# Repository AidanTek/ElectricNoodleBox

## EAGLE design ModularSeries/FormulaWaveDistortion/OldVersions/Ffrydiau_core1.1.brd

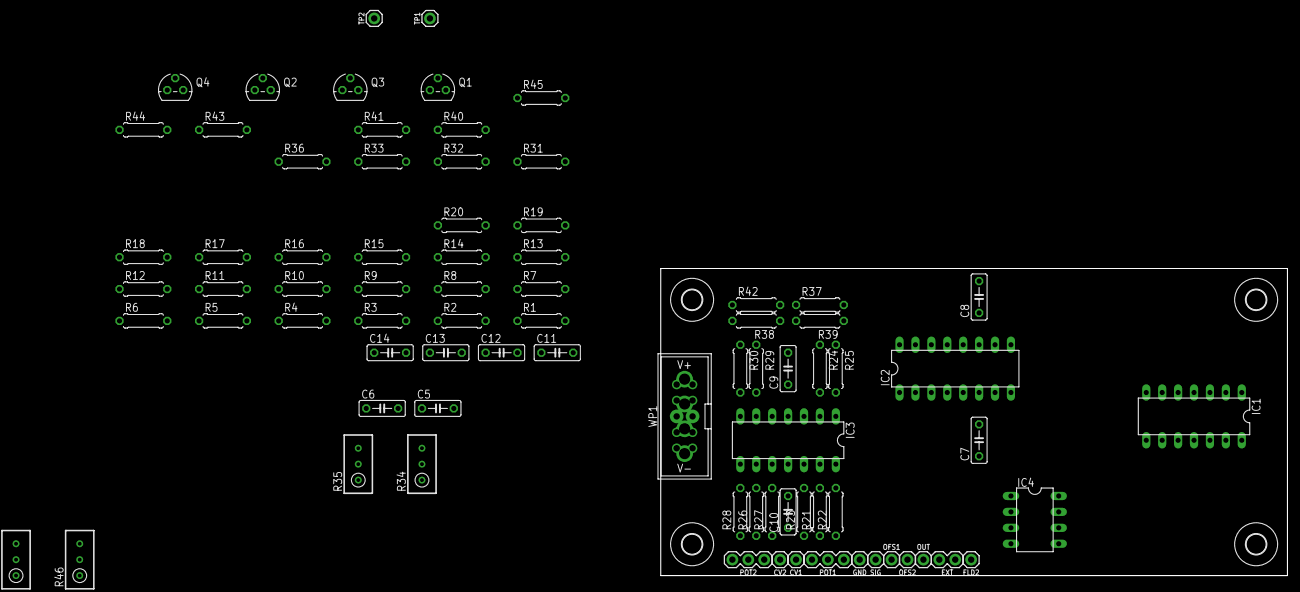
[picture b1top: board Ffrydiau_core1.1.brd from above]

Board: 2 copper layers, 100.0 x 49.0 mm, 83 parts (0 on the bottom side), 48 nets, no tracks yet.

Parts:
C5, C6, C7, C8, C9, C10, C11, C12: 100nF; C050-025X075
C13, C14: 22pF; C050-025X075
CV1, CV2: 1XWIREPAD; 1X01
EXT: 2XWIREPAD; 1X02
FLD2: 1XWIREPAD; 1X01
GND: 1XWIREPAD; 1X01
H1, H2, H3, H4: MOUNT-HOLE3.2; 3,2
IC1, IC3: DIL14
IC2: DIL16
IC4: DIL08
OFS1, OFS2: 1XWIREPAD; 1X01
OUT: 1XWIREPAD; 1X01
POT1, POT2: 3XWIREPAD; 1X03
Q1, Q3: 2N3906; TO92
Q2, Q4: 2N3904; TO92
R1, R12: 30K; 0207/7
R2, R3, R13, R14: 12K; 0207/7
R4, R16: 220K; 0207/7
R5, R6, R7, R15, R41, R44: 10K; 0207/7
R8, R9, R10, R11, R21, R22, R23, R24, R25, R26, R27, R28, R29, R30: 100K; 0207/7
R17, R18: 75K; 0207/7
R19, R20: 22K; 0207/7
R31, R32: 5K7; 0207/7
R33, R36: 15K; 0207/7
R34, R35, R46, R47: 10K; RTRIM3296W
R37, R38, R39, R40, R42, R43: 47K; 0207/7
R45: 100Ω; 0207/7
SIG: 1XWIREPAD; 1X01
TP1, TP2: 1XWIREPAD; 1X01
WP1: COMBO_SUPPLY_HEADER; COMBINED_POWER

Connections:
+12V: C6.1, C8.1, C9.1, C12.1, IC1.4, IC2.11, IC3.4, IC4.8, POT1.3, POT2.3, R2.2, R13.2, R31.1, R32.1, WP1.V+1, WP1.V+2, WP1.V+3
-12V: C5.2, C7.2, C10.2, C11.2, IC1.11, IC2.6, IC3.11, IC4.4, POT1.1, POT2.1, R3.1, R14.1, R37.1, R42.1, WP1.V-1, WP1.V-2, WP1.V-3
AGND: C5.1, C6.2, C7.1, C8.2, C9.2, C10.1, C11.1, C12.2, GND.1, IC1.3, IC1.5, IC1.10, IC1.12, IC3.3, IC3.5, IC3.10, IC3.12, IC4.3, IC4.5, R19.1, R20.1, R34.2, R35.2, R41.2, R44.2, WP1.GND1, WP1.GND2, WP1.GND3, WP1.GND4, WP1.GND5, WP1.GND6, WP1.GND7, WP1.GND8
unnamed: Q1.2, Q2.2, R1.2, R40.1
unnamed: Q1.3, R2.1, R46.3
unnamed: Q2.3, R3.2, R46.1
unnamed: Q1.1, Q2.1, R5.2, R46.2
unnamed: IC1.9, R4.2, R5.1
unnamed: IC1.8, R4.1, R6.2
unnamed: IC1.13, R6.1, R7.2
unnamed: OUT.1, R45.1
unnamed: C13.2, IC4.1, R1.1, R17.2, TP1.1
unnamed: IC1.2, R8.2, R9.1, R10.1, R11.1
unnamed: IC1.1, R8.1, R45.2
unnamed: Q3.2, Q4.2, R12.2, R43.1
unnamed: Q3.3, R13.1, R47.3
unnamed: Q4.3, R14.2, R47.1
unnamed: Q3.1, Q4.1, R15.2, R47.2
unnamed: IC1.6, R15.1, R16.2
unnamed: FLD2.1, IC1.7, R11.2, R16.1
unnamed: C14.1, IC2.12, IC4.6, R18.1, R20.2
unnamed: C13.1, IC2.5, IC4.2, R17.1, R19.2
unnamed: C14.2, IC4.7, R12.1, R18.2, TP2.1
unnamed: IC3.13, R21.2, R22.1, R23.2
unnamed: IC3.14, R22.2, R24.1
unnamed: IC3.2, R24.2, R25.1
unnamed: IC3.1, R25.2, R39.2
unnamed: CV2.1, R27.1
unnamed: IC3.7, R30.2, R38.2
unnamed: POT1.2, R21.1
unnamed: IC3.6, R29.2, R30.1
unnamed: CV1.1, R23.1
unnamed: IC3.8, R28.2, R29.1
unnamed: IC3.9, R26.2, R27.2, R28.1
unnamed: IC2.14, R35.3, R36.2
unnamed: IC2.13, R35.1
unnamed: IC2.15, R31.2
unnamed: IC2.2, R32.2
unnamed: IC2.1, R37.2, R39.1
unnamed: POT2.2, R26.1
unnamed: IC2.3, R33.2, R34.3
unnamed: IC2.4, R34.1
unnamed: IC2.16, R38.1, R42.2
unnamed: OFS1.1, R40.2, R41.1
unnamed: OFS2.1, R43.2, R44.1
unnamed: EXT.2, R36.1
SIGIN: R9.2, R33.1, SIG.1
STAGE1OUT: EXT.1, IC1.14, R7.1, R10.2

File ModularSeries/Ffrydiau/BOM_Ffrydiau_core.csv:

Qty,Value,Package,Parts,Description,RETAILER,CATALOGUE
,,,,,,
16,100K,0207/10,"R4, R8, R9, R10, R11, R16, R21, R22, R23, R24, R25, R26, R27, R28, R29, R30",RESISTOR 1/4W,Farnell,2329853
2,100Ω,0207/10,"R45, R46",RESISTOR 1/4W,Farnell,2329854
7,10K,0207/10,"R5, R6, R7, R12, R15, R41, R44",RESISTOR 1/4W,Farnell,2329855
4,12K,0207/10,"R2, R3, R13, R14",RESISTOR 1/4W,Farnell,2329863
2,15K,0207/10,"R33, R36",RESISTOR 1/4W,Farnell,1563095
2,22K,0207/10,"R19, R20",RESISTOR 1/4W,Farnell,2329901
6,47K,0207/10,"R37, R38, R39, R40, R42, R43",RESISTOR 1/4W,Farnell,2329944
1,4K7,0207/10,R1,RESISTOR 1/4W,Farnell,2329945
2,5K6,0207/10,"R31, R32",RESISTOR 1/4W,Farnell,2329958
2,75K,0207/10,"R17, R18",RESISTOR 1/4W,Farnell,2329972
2,10K,RTRIM3296W,"R34, R35",Trimm resistor 3296W,Farnell,9353186
,,,,,,
2,22pF,C050-025X075,"C13, C14",CAPACITOR Ceramic,Farnell,1457695
8,100nF,C050-025X075,"C5, C6, C7, C8, C9, C10, C11, C12",CAPACITOR Ceramic,Farnell,2797801
3,4.7¬µF,"E2,5-6E","C1, C2, C3","POLARIZED CAPACITOR, Electrolytic 25V+",Farnell,9451234
,,,,,,
2,2N3904,TO92,"Q2, Q4",NPN Transistor TO-92,Farnell,1574370
2,2N3906,TO92,"Q1, Q3",PNP Transistor TO-92,Farnell,1574372
1,LM13700,DIL16,IC2,Dual Transconductance Amplifier with Darlington Buffer,Farnell,3118206
1,TL082,DIL08,IC4,Dual Operational Amplifier,Farnell,1103189
2,TL084,DIL14,"IC1, IC3",Quad Operational Amplifier,Farnell,3005140
,,,,,,
1,Power Header,Power Header,WP1,10 way Shrouded IDC,Farnell,2843527
,,,,,,
9,Jack / Banana Connector,1X01,"CV1, CV2, FLD2, OFS1, OFS2, OUT, SIG, VCA",Banana or Jack patch point (panel part),Farnell,1698951
1,SPDT Mechanical Switch,1X02,EXT,Toggle switch SPDT (panel part),Farnell,9473491
2,B100K Potentiometer,1X03,"POT1, POT2",Taiwan Alpha 16mm (panel part),Rapid,65-0756

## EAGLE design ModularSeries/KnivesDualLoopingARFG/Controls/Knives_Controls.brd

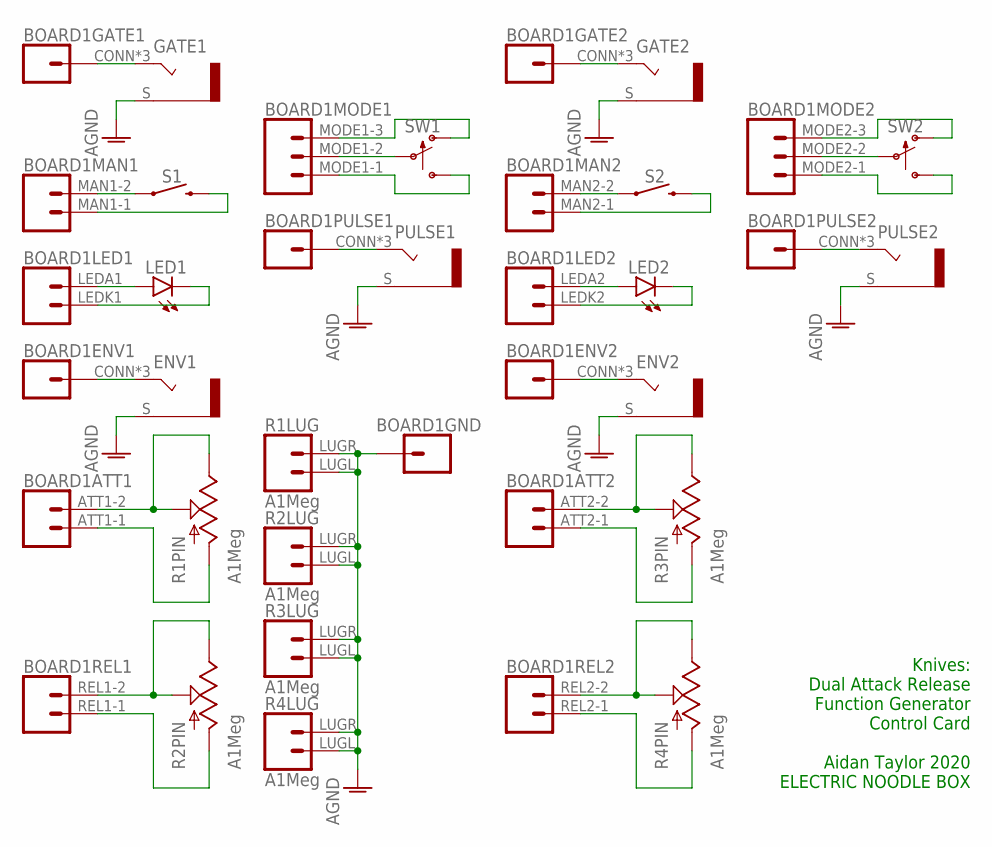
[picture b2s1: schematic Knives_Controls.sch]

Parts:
BOARD1: KNIVES_LINK; KNIVES
ENV1, ENV2: COMBI-JACKCINCHNANA; NEWCOMBOJACK_PANEL
GATE1, GATE2: COMBI-JACKCINCHNANA; NEWCOMBOJACK_PANEL
LED1, LED2: LED3MM
PULSE1, PULSE2: COMBI-JACKCINCHNANA; NEWCOMBOJACK_PANEL
R1, R2, R3, R4: A1Meg; ALPHA_RV09_9MMPOT
S1, S2: MCDTS-2_PUSHBUTTON
SW1, SW2: SPDT_SWITCHDW1; MICRODPDT-DW1

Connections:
AGND: BOARD1.GND (1), ENV1.S, ENV2.S, GATE1.S, GATE2.S, PULSE1.S, PULSE2.S, R1.LUGL (1), R1.LUGR (2), R2.LUGL (1), R2.LUGR (2), R3.LUGL (1), R3.LUGR (2), R4.LUGL (1), R4.LUGR (2)
unnamed: BOARD1.G1 (1), GATE1.CONN (T), GATE1.T1 (T), GATE1.T2 (T)
unnamed: BOARD1.MAN1-2 (2), S1.P$1 (1), S1.P$2 (1)
unnamed: BOARD1.MAN1-1 (1), S1.P$3 (2), S1.P$4 (2)
unnamed: BOARD1.LEDA1 (2), LED1.A
unnamed: BOARD1.LEDK1 (1), LED1.K (C)
unnamed: BOARD1.EOUT1 (1), ENV1.CONN (T), ENV1.T1 (T), ENV1.T2 (T)
unnamed: BOARD1.ATT1-2 (2), R1.C2 (W), R1.C3 (B)
unnamed: BOARD1.ATT1-1 (1), R1.C1 (A)
unnamed: BOARD1.REL1-2 (2), R2.C2 (W), R2.C3 (B)
unnamed: BOARD1.REL1-1 (1), R2.C1 (A)
unnamed: BOARD1.MODE1-1 (1), SW1.C3 (S)
unnamed: BOARD1.MODE1-2 (2), SW1.C2
unnamed: BOARD1.MODE1-3 (3), SW1.C1 (O)
unnamed: BOARD1.P1 (1), PULSE1.CONN (T), PULSE1.T1 (T), PULSE1.T2 (T)
unnamed: BOARD1.G2 (1), GATE2.CONN (T), GATE2.T1 (T), GATE2.T2 (T)
unnamed: BOARD1.MAN2-2 (2), S2.P$1 (1), S2.P$2 (1)
unnamed: BOARD1.MAN2-1 (1), S2.P$3 (2), S2.P$4 (2)
unnamed: BOARD1.LEDA2 (2), LED2.A
unnamed: BOARD1.LEDK2 (1), LED2.K (C)
unnamed: BOARD1.EOUT2 (1), ENV2.CONN (T), ENV2.T1 (T), ENV2.T2 (T)
unnamed: BOARD1.ATT2-2 (2), R3.C2 (W), R3.C3 (B)
unnamed: BOARD1.ATT2-1 (1), R3.C1 (A)
unnamed: BOARD1.REL2-2 (2), R4.C2 (W), R4.C3 (B)
unnamed: BOARD1.REL2-1 (1), R4.C1 (A)
unnamed: BOARD1.MODE2-1 (1), SW2.C3 (S)
unnamed: BOARD1.MODE2-2 (2), SW2.C2
unnamed: BOARD1.MODE2-3 (3), SW2.C1 (O)
unnamed: BOARD1.P2 (1), PULSE2.CONN (T), PULSE2.T1 (T), PULSE2.T2 (T)

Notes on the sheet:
Knives: Dual Attack Release Function Generator Control Card Aidan Taylor 2020 ELECTRIC NOODLE BOX

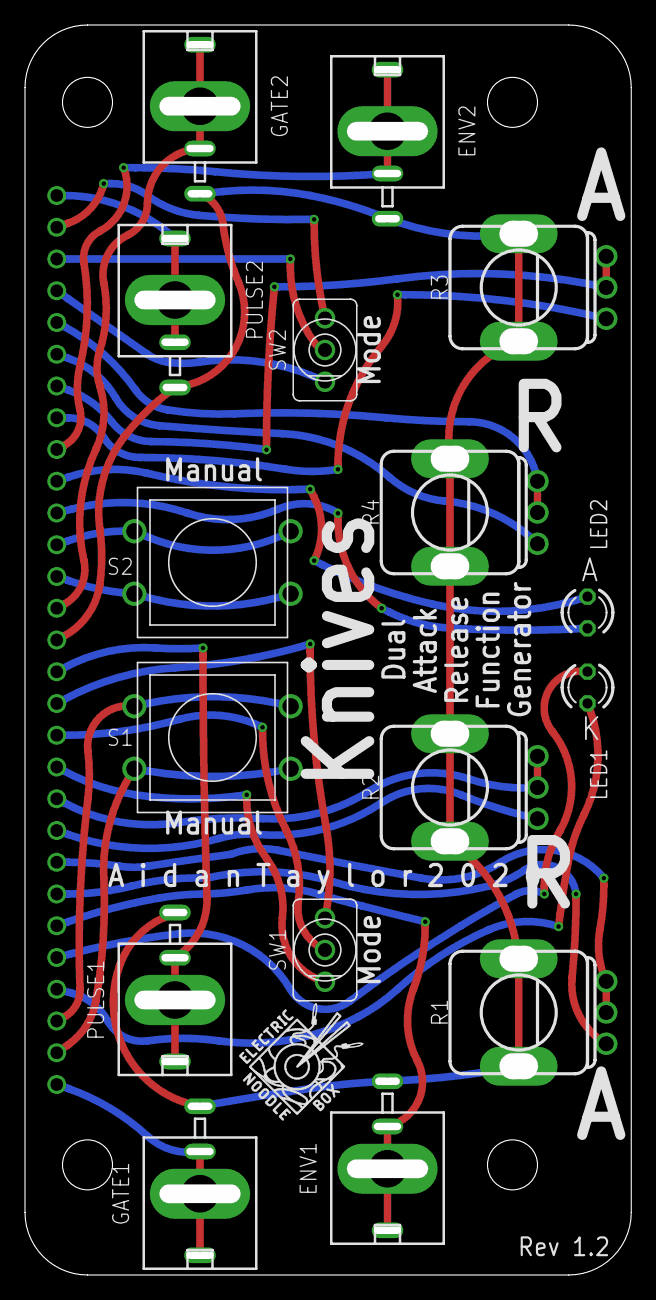
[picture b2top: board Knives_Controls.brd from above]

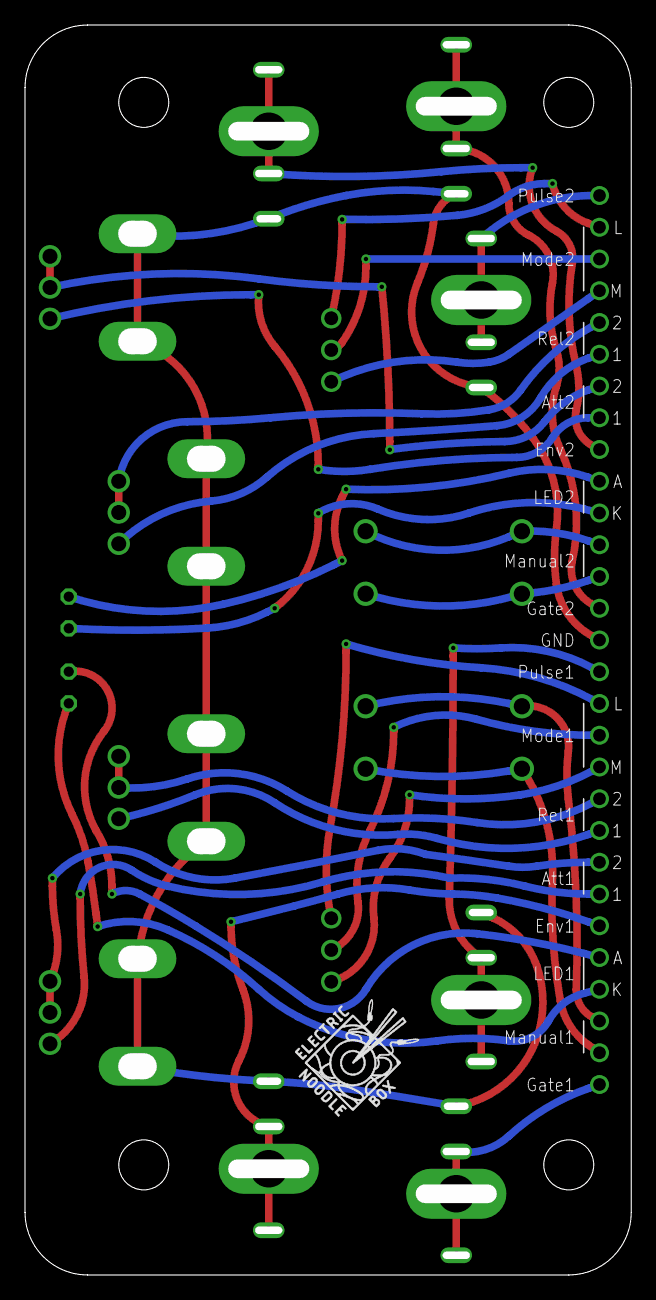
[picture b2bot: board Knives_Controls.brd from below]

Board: 2 copper layers, 48.5 x 100.0 mm, 19 parts (2 on the bottom side), 29 nets.

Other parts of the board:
U$1, U$2: LOGO10X10

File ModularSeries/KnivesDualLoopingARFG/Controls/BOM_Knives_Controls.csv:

Qty,Value,Package,Parts,Description,Retailer,Catalogue
2,,LED3MM,"LED1, LED2",LED 3mm Red,Farnell,1581121
4,A1Meg,ALPHA_RV09_9MMPOT,"R1, R2, R3, R4",Taiwan Alpha 9mm Potentiometer,Thonk,D-shaft A1M
2,BANANA_PANEL,BANANA_PANEL,"ENV1, ENV2",Cinch Green Banana Socket,Mouser,530-1080904-1
2,BANANA_PANEL,BANANA_PANEL,"PULSE1, PULSE2",Cinch White Banana Socket,Mouser,530-108-0901-1
2,BANANA_PANEL,BANANA_PANEL,"GATE1, GATE2",Cinch Violet Banana Socket,Mouser,530-108-0912-1
2,MCDTS-2_PUSHBUTTON,MCDTS-2_PUSHBUTTON,"S1, S2",MCDTS-2 Series Momentary Switch,Farnell,2543105
2,SPDT_SWITCHDW1,MICRODPDT-DW1,"SW1, SW2",SPDT Dailywell Toggle Switch,Thonk,DW1
2,MCDTS-2 Cap,MCDTS-2 Cap,"S1, S2",MCDTS-2 Series Cap KTSC-22R Red,Farnell,9561536
4,Small Knob,Small Knob,"R1, R2, R3, R4",SIFAM/SELCO Small Grey,Thonk,Small Grey
4,Small Green Cap,Small Green Cap,"R1, R2, R3, R4",SIFAM/SELCO Cap Green Small,Thonk,Small Green
4,Male Header,Male Header,,8way 1row 2.54mm Header Male,Farnell,2856626
4,Female Header,Female Header,,8way 1row 2.54mm Header Female,Farnell,1668208
4,M3 Standoff,M3 Standoff,,8mm Standoff Nylon,Farnell,1466945
4,M3 Screw,M3 Screw,,Stainless Steel M3,Farnell,1420032

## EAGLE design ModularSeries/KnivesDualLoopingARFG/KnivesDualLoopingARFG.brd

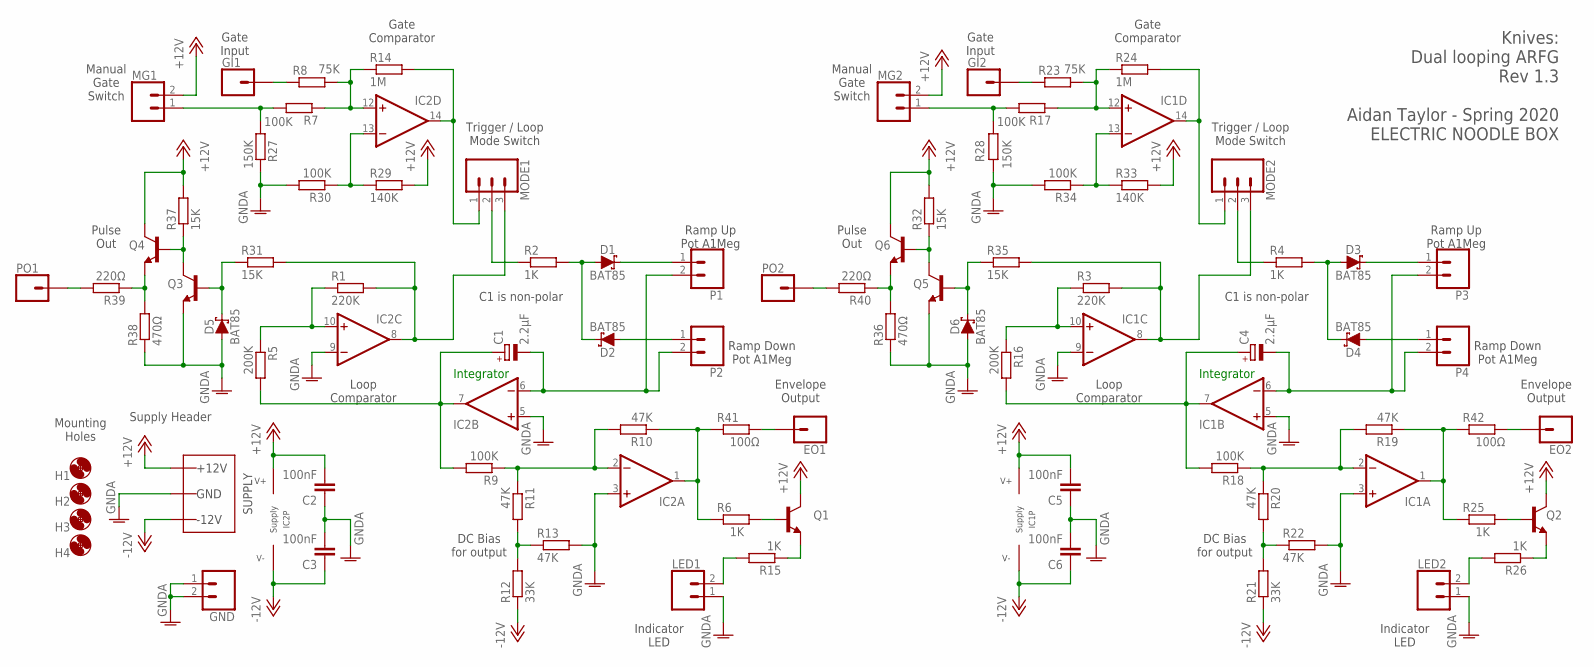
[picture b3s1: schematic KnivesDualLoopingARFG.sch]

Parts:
C1, C4: 2.2µF; E2-5
C2, C3, C5, C6: 100nF; C050-025X075
D1, D2, D3, D4, D5, D6: BAT85; DO35-7
EO1, EO2: 1XWIREPAD; 1X01
GI1, GI2: 1XWIREPAD; 1X01
GND: 2XWIREPAD; 1X02
H1, H2, H3, H4: MOUNT-HOLE3.2; 3,2
IC1, IC2: TL0X4DIL; DIL14
LED1, LED2: 2XWIREPAD; 1X02
MG1, MG2: 2XWIREPAD; 1X02
MODE1, MODE2: 3XWIREPAD; 1X03
P1, P2, P3, P4: 2XWIREPAD; 1X02
PO1, PO2: 1XWIREPAD; 1X01
Q1, Q2, Q3, Q4, Q5, Q6: 2N3904; TO92
R1, R3: 220K; 0207/10
R2, R4, R6, R15, R25, R26: 1K; 0207/10
R5, R16: 200K; 0207/10
R7, R9, R17, R18, R30, R34: 100K; 0207/10
R8, R23: 75K; 0207/10
R10, R11, R13, R19, R20, R22: 47K; 0207/10
R12, R21: 33K; 0207/10
R14, R24: 1M; 0207/10
R27, R28: 150K; 0207/10
R29, R33: 140K; 0207/10
R31, R32, R35, R37: 15K; 0207/10
R36, R38: 470Ω; 0207/10
R39, R40: 220Ω; 0207/10
R41, R42: 100Ω; 0207/10
WP1: COMBO_SUPPLY_HEADER; COMBINED_POWER

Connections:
+12V: C2.2, C5.2, IC1.4 (V+), IC2.4 (V+), MG1.2, MG2.2, Q1.1 (C), Q2.1 (C), Q4.1 (C), Q6.1 (C), R29.2, R32.2, R33.2, R37.2, WP1.V+1 (V++), WP1.V+2 (V++), WP1.V+3 (V++)
-12V: C3.1, C6.1, IC1.11 (V-), IC2.11 (V-), R12.1, R21.1, WP1.V-1 (V--), WP1.V-2 (V--), WP1.V-3 (V--)
ENV1_TRIG: GI1.1, R8.1
ENV1_TRIG1: GI2.1, R23.1
ENVELOPE_OUTPUT: IC2.1 (OUT), R6.1, R10.1, R41.1
ENVELOPE_OUTPUT1: IC1.1 (OUT), R19.1, R25.1, R42.1
GNDA: C2.1, C3.2, C5.1, C6.2, D5.A, D6.A, GND.1, GND.2, IC1.3 (+IN), IC1.5 (+IN), IC1.9 (-IN), IC2.3 (+IN), IC2.5 (+IN), IC2.9 (-IN), LED1.1, LED2.1, Q3.3 (E), Q5.3 (E), R13.2, R22.2, R27.2, R28.2, R30.2, R34.2, R36.1, R38.1, WP1.GND1 (AGND), WP1.GND2 (AGND), WP1.GND3 (AGND), WP1.GND4 (AGND), WP1.GND5 (AGND), WP1.GND6 (AGND), WP1.GND7 (AGND), WP1.GND8 (AGND)
unnamed: Q5.1 (C), Q6.2 (B), R32.1
unnamed: D1.A, D2.C, R2.2
unnamed: D1.C, P1.1
unnamed: D2.A, P2.1
unnamed: C1.-, IC2.6 (-IN), P1.2, P2.2
unnamed: Q1.2 (B), R6.2
unnamed: C1.+, IC2.7 (OUT), R5.2, R9.2
unnamed: IC2.10 (+IN), R1.1, R5.1
unnamed: IC2.2 (-IN), R9.1, R10.2, R11.1
unnamed: Q1.3 (E), R15.1
unnamed: R11.2, R12.2, R13.1
unnamed: MG1.1, R7.2, R27.1
unnamed: IC2.12 (+IN), R7.1, R8.2, R14.1
unnamed: MODE1.2, R2.1
unnamed: IC2.14 (OUT), MODE1.1, R14.2
unnamed: LED1.2, R15.2
unnamed: IC1.8 (OUT), MODE2.3, R3.2, R35.2
unnamed: D3.A, D4.C, R4.2
unnamed: D4.A, P4.1
unnamed: C4.-, IC1.6 (-IN), P3.2, P4.2
unnamed: C4.+, IC1.7 (OUT), R16.2, R18.2
unnamed: IC1.10 (+IN), R3.1, R16.1
unnamed: IC1.2 (-IN), R18.1, R19.2, R20.1
unnamed: R20.2, R21.2, R22.1
unnamed: MG2.1, R17.2, R28.1
unnamed: IC1.12 (+IN), R17.1, R23.2, R24.1
unnamed: IC1.14 (OUT), MODE2.1, R24.2
unnamed: MODE2.2, R4.1
unnamed: Q2.2 (B), R25.2
unnamed: Q2.3 (E), R26.1
unnamed: LED2.2, R26.2
unnamed: D3.C, P3.1
unnamed: IC2.13 (-IN), R29.1, R30.1
unnamed: D5.C, Q3.2 (B), R31.1
unnamed: IC1.13 (-IN), R33.1, R34.1
unnamed: D6.C, Q5.2 (B), R35.1
unnamed: Q3.1 (C), Q4.2 (B), R37.1
unnamed: Q4.3 (E), R38.2, R39.1
unnamed: IC2.8 (OUT), MODE1.3, R1.2, R31.2
unnamed: Q6.3 (E), R36.2, R40.1
unnamed: PO1.1, R39.2
unnamed: PO2.1, R40.2
unnamed: EO1.1, R41.2
unnamed: EO2.1, R42.2

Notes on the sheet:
DC Bias for output
Integrator
Gate Comparator
Loop Comparator
Trigger / Loop Mode Switch
C1 is non-polar
Ramp Up Pot A1Meg
Ramp Down Pot A1Meg
Indicator LED
Manual Gate Switch
Gate Input
Envelope Output
Knives: Dual looping ARFG Rev 1.3 Aidan Taylor - Spring 2020 ELECTRIC NOODLE BOX
Supply Header
Mounting Holes
Pulse Out

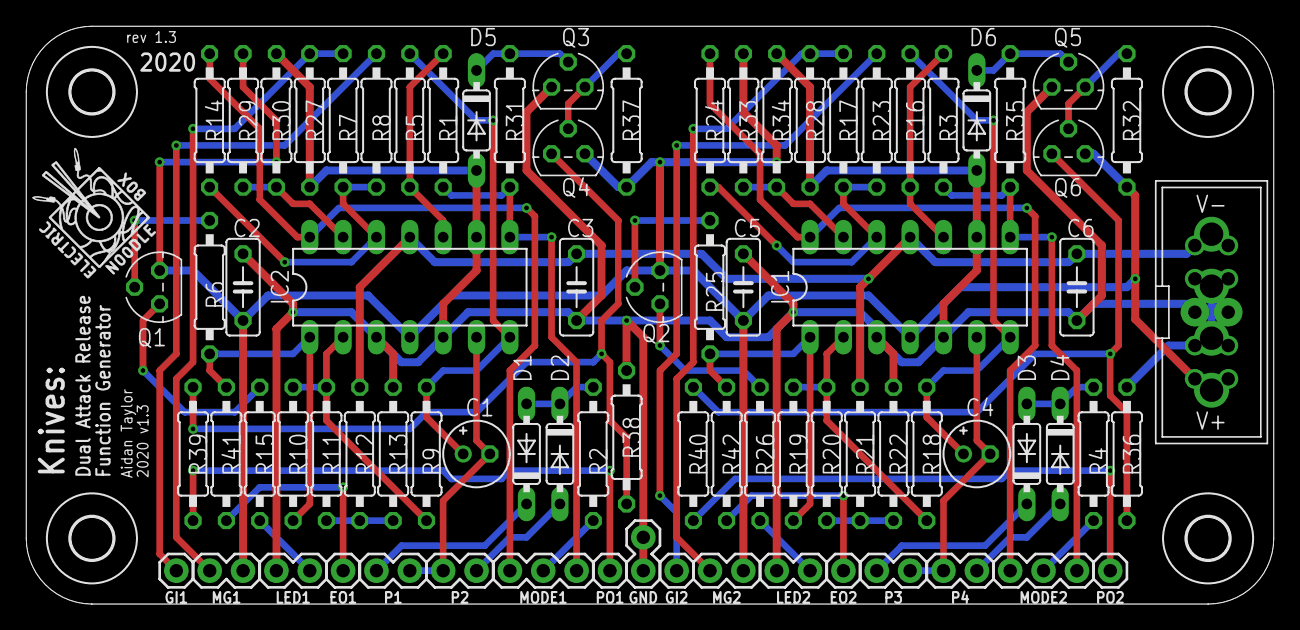
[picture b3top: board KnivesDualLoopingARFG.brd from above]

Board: 2 copper layers, 95.0 x 44.0 mm, 86 parts (1 on the bottom side), 51 nets.

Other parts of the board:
U$1, U$2: LOGO10X10

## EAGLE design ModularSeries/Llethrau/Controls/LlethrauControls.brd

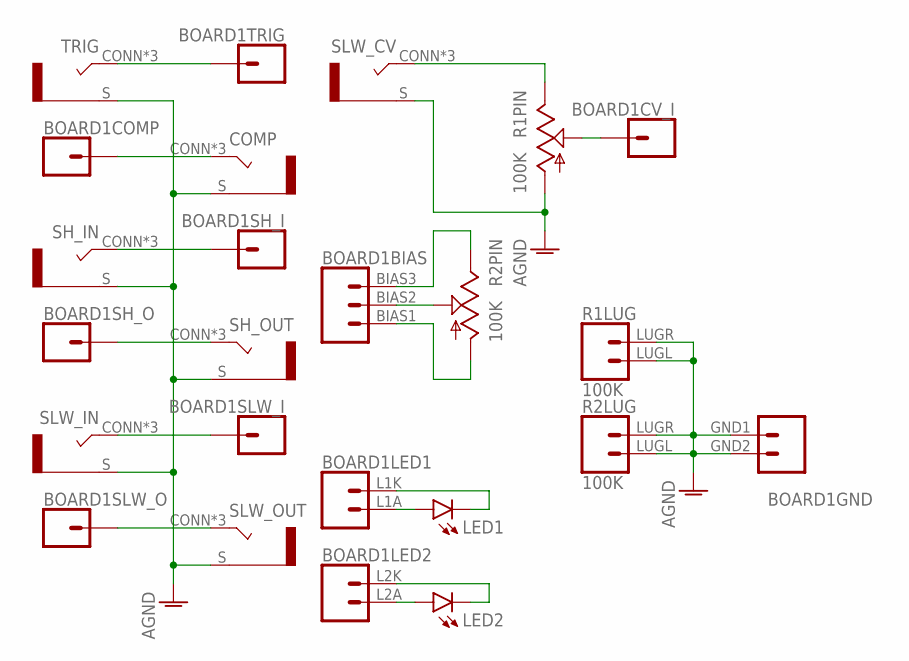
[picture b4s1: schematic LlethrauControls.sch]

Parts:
BOARD1: LLETHRAU_LINK; LLETHRAU
COMP: COMBI-JACKCINCHNANA; NEWCOMBOJACK_PANEL
LED1, LED2: LED5MM
R1, R2: 100K; ALPHA_RV09_9MMPOT
SH_IN: COMBI-JACKCINCHNANA; NEWCOMBOJACK_PANEL
SH_OUT: COMBI-JACKCINCHNANA; NEWCOMBOJACK_PANEL
SLW_CV: COMBI-JACKCINCHNANA; NEWCOMBOJACK_PANEL
SLW_IN: COMBI-JACKCINCHNANA; NEWCOMBOJACK_PANEL
SLW_OUT: COMBI-JACKCINCHNANA; NEWCOMBOJACK_PANEL
TRIG: COMBI-JACKCINCHNANA; NEWCOMBOJACK_PANEL

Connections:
AGND: BOARD1.GND1 (1), BOARD1.GND2 (2), COMP.S, R1.C1 (A), R1.LUGL (1), R1.LUGR (2), R2.LUGL (1), R2.LUGR (2), SH_IN.S, SH_OUT.S, SLW_CV.S, SLW_IN.S, SLW_OUT.S, TRIG.S
unnamed: BOARD1.TRIG (1), TRIG.CONN (T), TRIG.T1 (T), TRIG.T2 (T)
unnamed: BOARD1.COMP (1), COMP.CONN (T), COMP.T1 (T), COMP.T2 (T)
unnamed: BOARD1.SH_I (1), SH_IN.CONN (T), SH_IN.T1 (T), SH_IN.T2 (T)
unnamed: BOARD1.SH_O (1), SH_OUT.CONN (T), SH_OUT.T1 (T), SH_OUT.T2 (T)
unnamed: BOARD1.SLW_I (1), SLW_IN.CONN (T), SLW_IN.T1 (T), SLW_IN.T2 (T)
unnamed: BOARD1.SLW_O (1), SLW_OUT.CONN (T), SLW_OUT.T1 (T), SLW_OUT.T2 (T)
unnamed: BOARD1.BIAS1 (1), R2.C1 (A)
unnamed: BOARD1.BIAS2 (2), R2.C2 (W)
unnamed: BOARD1.BIAS3 (3), R2.C3 (B)
unnamed: BOARD1.L2A (1), LED2.A
unnamed: R1.C3 (B), SLW_CV.CONN (T), SLW_CV.T1 (T), SLW_CV.T2 (T)
unnamed: BOARD1.CV_I (1), R1.C2 (W)
unnamed: BOARD1.L2K (2), LED2.K (C)
unnamed: BOARD1.L1A (1), LED1.A
unnamed: BOARD1.L1K (2), LED1.K (C)

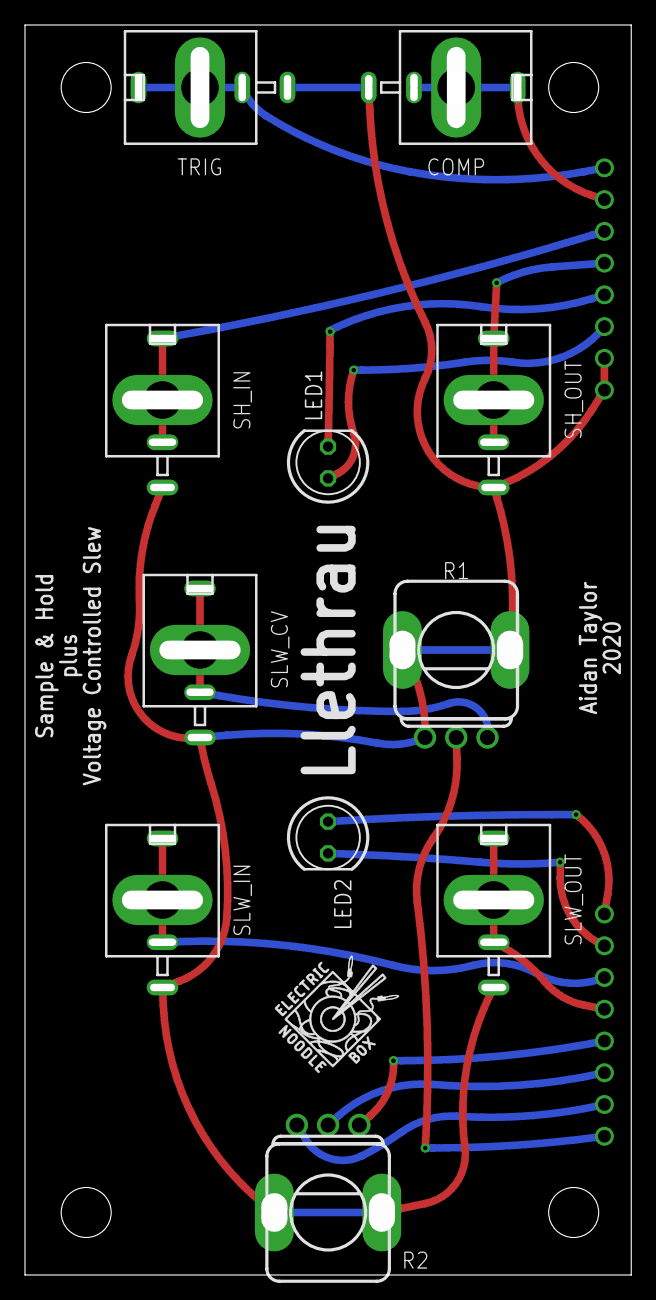
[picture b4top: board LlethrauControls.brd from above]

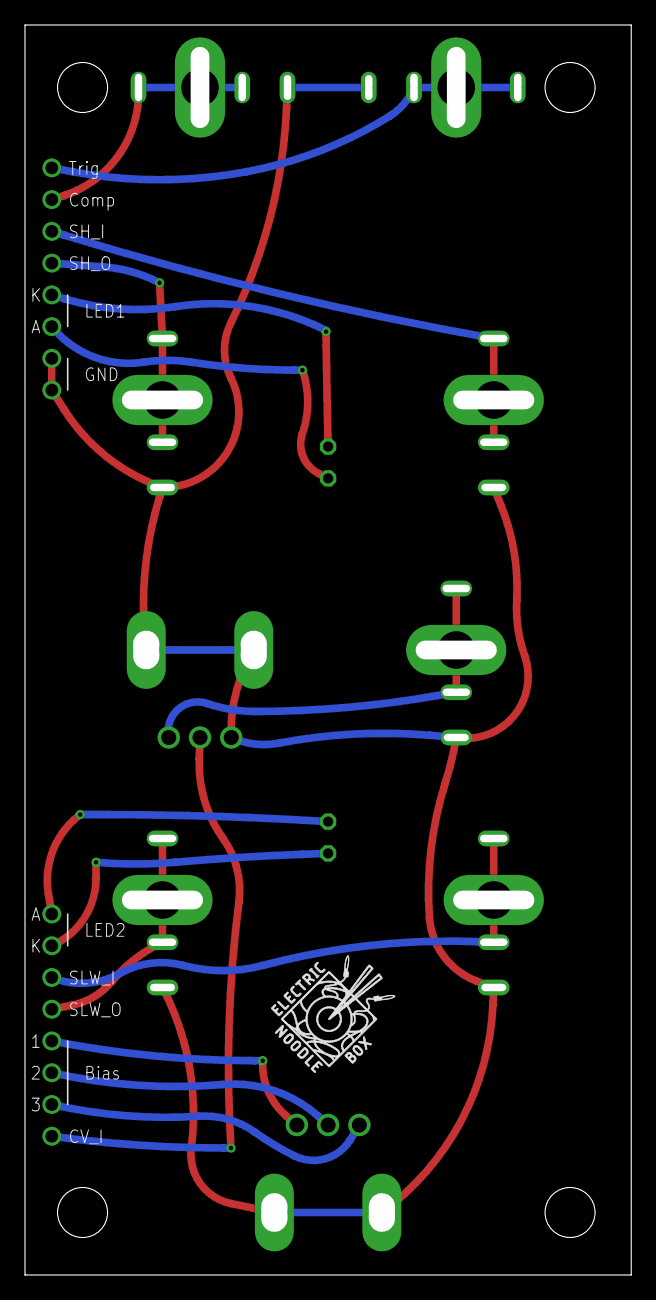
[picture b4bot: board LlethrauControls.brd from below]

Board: 2 copper layers, 48.5 x 100.0 mm, 14 parts (2 on the bottom side), 16 nets.

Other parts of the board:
U$1, U$2: LOGO10X10

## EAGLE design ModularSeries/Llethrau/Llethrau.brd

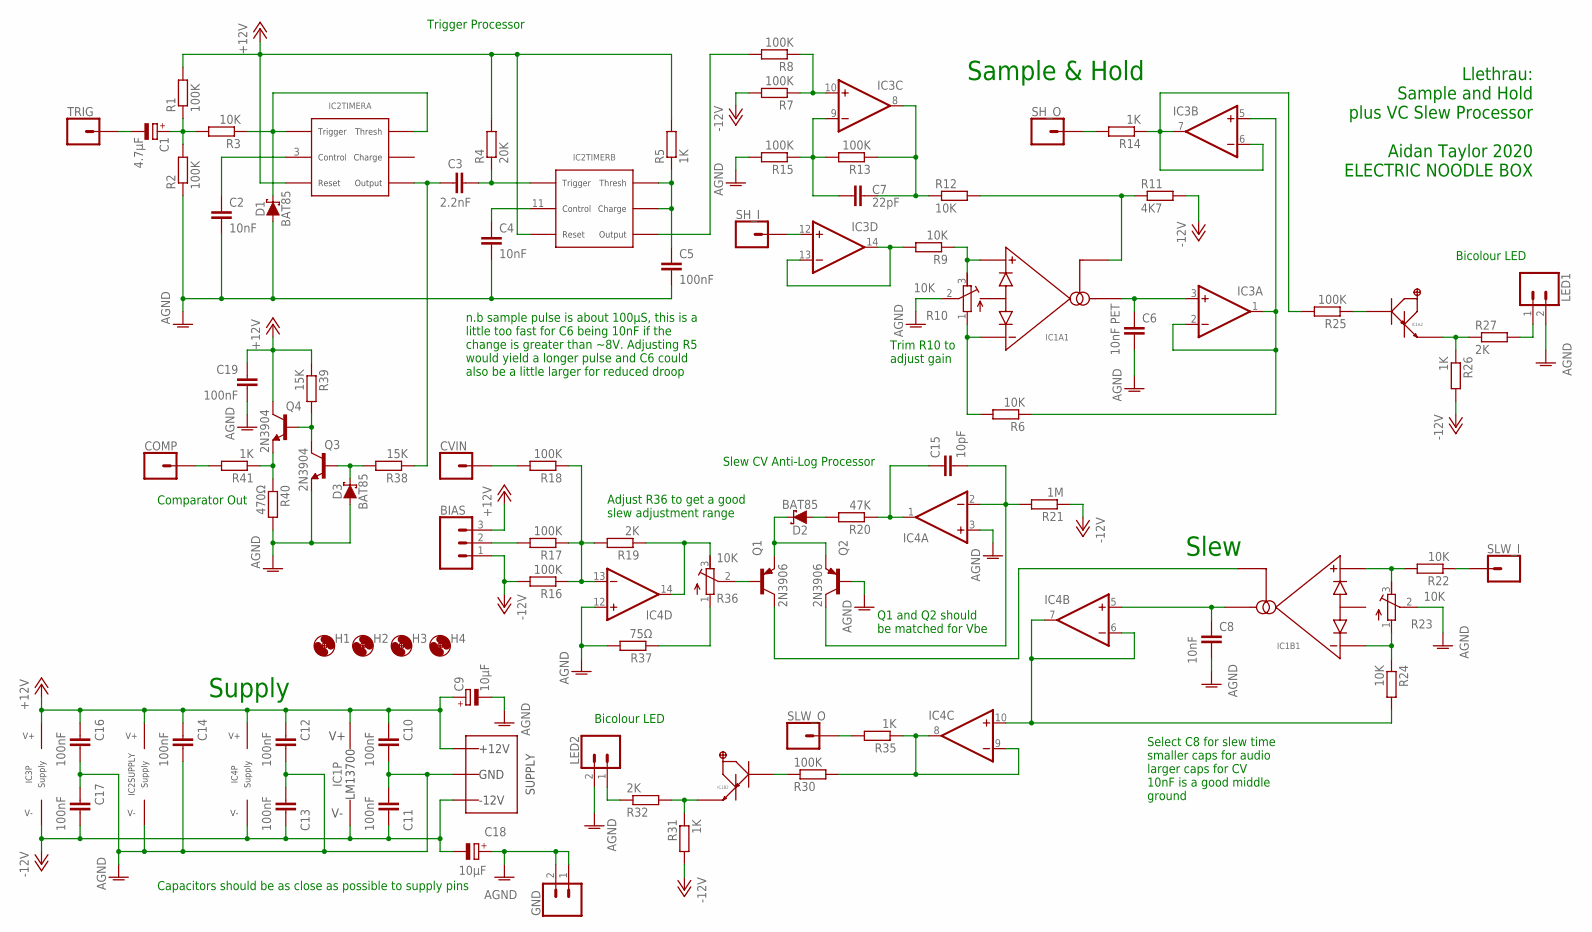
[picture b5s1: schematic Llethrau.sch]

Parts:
BIAS: 3XWIREPAD; 1X03
C1: 4.7µF; E2,5-5
C2, C4, C8: 10nF; C050-025X075
C3: 2.2nF; C050-025X075
C5, C10, C11, C12, C13, C14, C16, C17, C19: 100nF; C050-025X075
C6: 10nF PET; C050-025X075
C7: 22pF; C050-025X075
C9, C18: 10µF; E2,5-5
C15: 10pF; C050-025X075
COMP: 1XWIREPAD; 1X01
CVIN: 1XWIREPAD; 1X01
D1, D2, D3: BAT85; DO35-7
GND: 2XWIREPAD; 1X02
H1, H2, H3, H4: MOUNT-HOLE3.2; 3,2
IC1: LM13700DIL; DIL16
IC2: 556_DUALTIMERDIL14; DIL14
IC3, IC4: TL0X4DIL; DIL14
LED1, LED2: 2XWIREPAD; 1X02
Q1, Q2: 2N3906; TO92
Q3, Q4: 2N3904; TO92
R1, R2, R7, R8, R13, R15, R16, R17, R18, R25, R30: 100K; 0207/7
R3, R6, R9, R12, R22, R24: 10K; 0207/7
R4: 20K; 0207/7
R5, R14, R26, R31, R35, R41: 1K; 0207/7
R10, R23, R36: 10K; RTRIM3296W
R11: 4K7; 0207/7
R19, R27, R32: 2K; 0207/7
R20: 47K; 0207/7
R21: 1M; 0207/7
R37: 75Ω; 0207/7
R38, R39: 15K; 0207/7
R40: 470Ω; 0207/7
SH_I: 1XWIREPAD; 1X01
SH_O: 1XWIREPAD; 1X01
SLW_I: 1XWIREPAD; 1X01
SLW_O: 1XWIREPAD; 1X01
TRIG: 1XWIREPAD; 1X01
WP1: COMBO_SUPPLY_HEADER; COMBINED_POWER

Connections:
+12V: BIAS.3, C9.+, C10.1, C12.1, C14.1, C16.1, C19.1, IC1.11 (V+), IC2.4 (RESET), IC2.10 (RESET), IC2.14 (V+), IC3.4 (V+), IC4.4 (V+), Q4.1 (C), R1.2, R4.2, R5.2, R39.1, WP1.V+1 (V++), WP1.V+2 (V++), WP1.V+3 (V++)
-12V: BIAS.1, C11.2, C13.2, C17.2, C18.-, IC1.6 (V-), IC3.11 (V-), IC4.11 (V-), R7.2, R11.2, R16.2, R21.1, R26.2, R31.2, WP1.V-1 (V--), WP1.V-2 (V--), WP1.V-3 (V--)
AGND: C2.2, C4.2, C5.2, C6.2, C8.2, C9.-, C10.2, C11.1, C12.2, C13.1, C14.2, C16.2, C17.1, C18.+, C19.2, D1.A, D3.A, GND.1, GND.2, IC2.7 (V-), IC4.3 (+IN), IC4.12 (+IN), LED1.2, LED2.2, Q2.2 (B), Q3.3 (E), R2.1, R10.2 (S), R15.2, R23.2 (S), R37.2, R40.2, WP1.GND1 (AGND), WP1.GND2 (AGND), WP1.GND3 (AGND), WP1.GND4 (AGND), WP1.GND5 (AGND), WP1.GND6 (AGND), WP1.GND7 (AGND), WP1.GND8 (AGND)
unnamed: D1.C, IC2.2 (THRESHOLD), IC2.6 (TRIGGER), R3.1
unnamed: C1.+, R1.1, R2.2, R3.2
unnamed: LED1.1, R27.2
unnamed: C3.1, IC2.5 (OUTPUT), R38.1
unnamed: C5.1, IC2.12 (THRESHOLD), IC2.13 (DISCHARGE), R5.1
unnamed: C2.1, IC2.3 (CONT)
unnamed: C3.2, IC2.8 (TRIGGER), R4.1
unnamed: C4.1, IC2.11 (CONT)
unnamed: IC2.9 (OUTPUT), R8.2
unnamed: IC3.10 (+IN), R7.1, R8.1
unnamed: C7.2, IC3.8 (OUT), R12.1, R13.1
unnamed: C6.1, IC1.5 (AMPOUT), IC3.3 (+IN)
unnamed: IC3.1 (OUT), IC3.2 (-IN), IC3.5 (+IN), R6.1
unnamed: IC1.1 (AMPBIAS), R11.1, R12.2
unnamed: IC1.4 (AMP-), R6.2, R10.1 (A)
unnamed: IC1.3 (AMP+), R9.1, R10.3 (E)
unnamed: IC3.13 (-IN), IC3.14 (OUT), R9.2
unnamed: C1.-, TRIG.1
unnamed: IC3.12 (+IN), SH_I.1
unnamed: IC3.6 (-IN), IC3.7 (OUT), R14.1, R25.2
unnamed: R14.2, SH_O.1
unnamed: D2.C, Q1.3 (E), Q2.3 (E)
unnamed: C7.1, IC3.9 (-IN), R13.2, R15.1
unnamed: IC4.13 (-IN), R16.1, R17.1, R18.1, R19.2
unnamed: IC4.14 (OUT), R19.1, R36.3 (E)
unnamed: D2.A, R20.2
unnamed: IC4.6 (-IN), IC4.7 (OUT), IC4.10 (+IN), R24.2
unnamed: BIAS.2, R17.2
unnamed: CVIN.1, R18.2
unnamed: IC1.14 (AMP+), R22.2, R23.3 (E)
unnamed: R36.1 (A), R37.1
unnamed: Q1.2 (B), R36.2 (S)
unnamed: IC1.13 (AMP-), R23.1 (A), R24.1
unnamed: COMP.1, R41.2
unnamed: D3.C, Q3.2 (B), R38.2
unnamed: C8.1, IC1.12 (AMPOUT), IC4.5 (+IN)
unnamed: IC1.16 (AMPBIAS), Q1.1 (C)
unnamed: IC4.8 (OUT), IC4.9 (-IN), R30.2, R35.1
unnamed: IC1.7 (BUFF_IN), R25.1
unnamed: IC1.8 (BUFF_OUT), R26.1, R27.1
unnamed: LED2.1, R32.1
unnamed: IC1.10 (BUFF_IN), R30.1
unnamed: IC1.9 (BUFF_OUT), R31.1, R32.2
unnamed: R35.2, SLW_O.1
unnamed: C15.1, IC4.1 (OUT), R20.1
unnamed: C15.2, IC4.2 (-IN), Q2.1 (C), R21.2
unnamed: R22.1, SLW_I.1
unnamed: Q3.1 (C), Q4.2 (B), R39.2
unnamed: Q4.3 (E), R40.1, R41.1

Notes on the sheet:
Trim R10 to adjust gain
n.b sample pulse is about 100µS, this is a little too fast for C6 being 10nF if the change is greater than ~8V. Adjusting R5 would yield a longer pulse and C6 could also be a little larger for reduced droop
Select C8 for slew time smaller caps for audio larger caps for CV 10nF is a good middle ground
Sample & Hold
Slew
Supply
Capacitors should be as close as possible to supply pins
Bicolour LED
Llethrau: Sample and Hold plus VC Slew Processor Aidan Taylor 2020 ELECTRIC NOODLE BOX
Trigger Processor
Slew CV Anti-Log Processor
Adjust R36 to get a good slew adjustment range
Comparator Out
Q1 and Q2 should be matched for Vbe

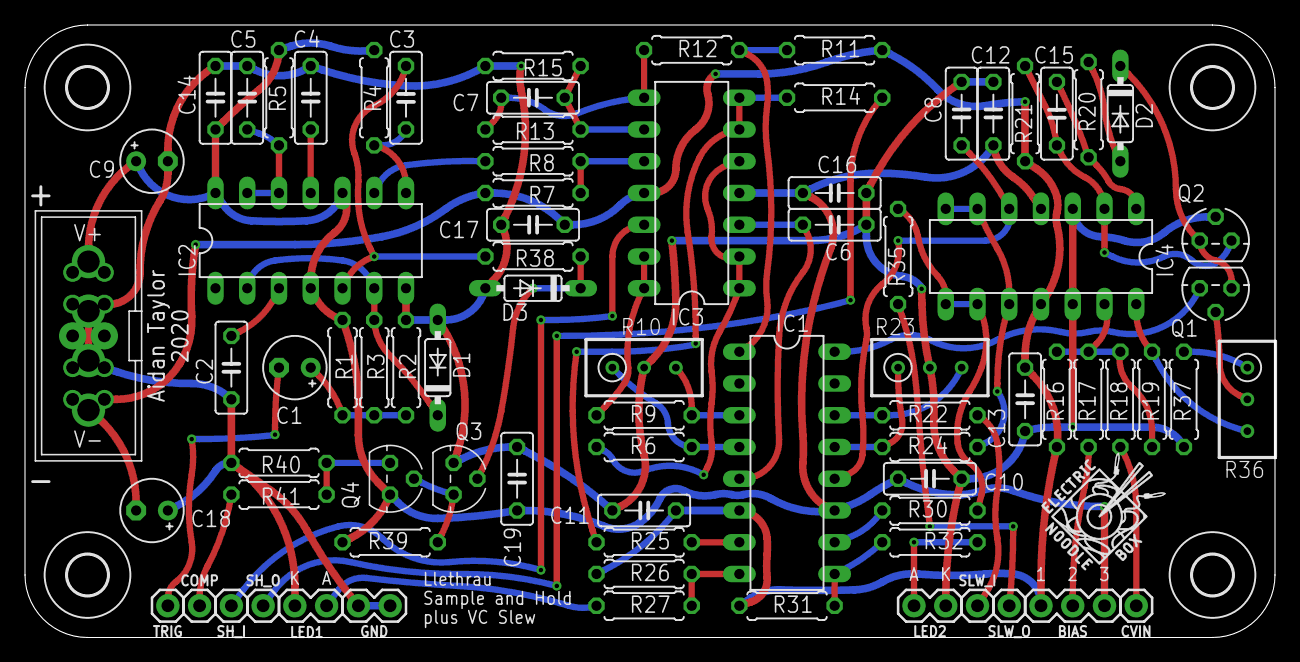
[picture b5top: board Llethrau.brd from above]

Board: 2 copper layers, 100.0 x 49.0 mm, 85 parts (1 on the bottom side), 52 nets.

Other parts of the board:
U$1, U$2: LOGO10X10

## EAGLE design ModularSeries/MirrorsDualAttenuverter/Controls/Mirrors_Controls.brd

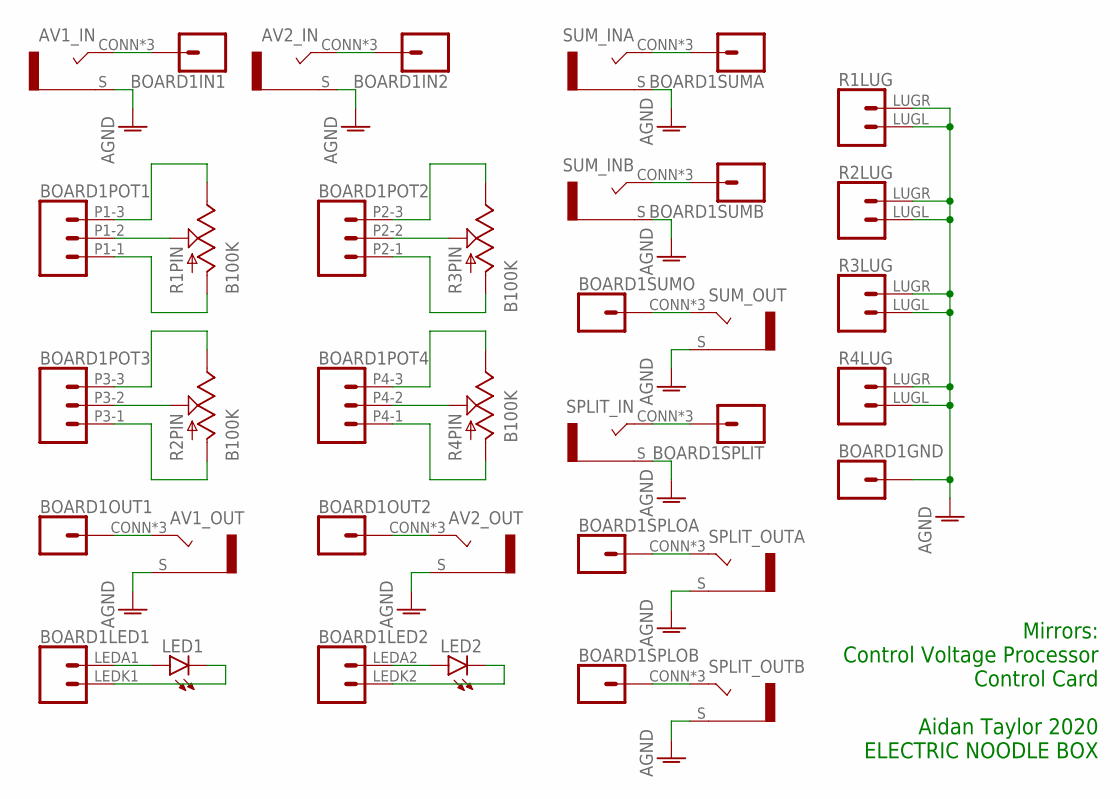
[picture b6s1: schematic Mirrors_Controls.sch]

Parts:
AV1_IN, AV1_OUT, AV2_IN, AV2_OUT: COMBI-JACKCINCHNANA; NEWCOMBOJACK_PANEL
BOARD1: MIRRORS_LINK; MIRRORS
LED1, LED2: LED5MM
R1, R2, R3, R4: B100K; ALPHA_RV09_9MMPOT
SPLIT_IN: COMBI-JACKCINCHNANA; NEWCOMBOJACK_PANEL
SPLIT_OUTA: COMBI-JACKCINCHNANA; NEWCOMBOJACK_PANEL
SPLIT_OUTB: COMBI-JACKCINCHNANA; NEWCOMBOJACK_PANEL
SUM_INA: COMBI-JACKCINCHNANA; NEWCOMBOJACK_PANEL
SUM_INB: COMBI-JACKCINCHNANA; NEWCOMBOJACK_PANEL
SUM_OUT: COMBI-JACKCINCHNANA; NEWCOMBOJACK_PANEL

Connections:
AGND: AV1_IN.S, AV1_OUT.S, AV2_IN.S, AV2_OUT.S, BOARD1.GND (1), R1.LUGL (1), R1.LUGR (2), R2.LUGL (1), R2.LUGR (2), R3.LUGL (1), R3.LUGR (2), R4.LUGL (1), R4.LUGR (2), SPLIT_IN.S, SPLIT_OUTA.S, SPLIT_OUTB.S, SUM_INA.S, SUM_INB.S, SUM_OUT.S
unnamed: AV1_IN.CONN (T), AV1_IN.T1 (T), AV1_IN.T2 (T), BOARD1.IN1 (1)
unnamed: BOARD1.P1-3 (3), R1.C3 (B)
unnamed: BOARD1.P1-2 (2), R1.C2 (W)
unnamed: BOARD1.P1-1 (1), R1.C1 (A)
unnamed: BOARD1.P3-3 (3), R2.C3 (B)
unnamed: BOARD1.P3-2 (2), R2.C2 (W)
unnamed: BOARD1.P3-1 (1), R2.C1 (A)
unnamed: AV1_OUT.CONN (T), AV1_OUT.T1 (T), AV1_OUT.T2 (T), BOARD1.OUT1 (1)
unnamed: BOARD1.LEDA1 (2), LED1.A
unnamed: BOARD1.LEDK1 (1), LED1.K (C)
unnamed: AV2_IN.CONN (T), AV2_IN.T1 (T), AV2_IN.T2 (T), BOARD1.IN2 (1)
unnamed: BOARD1.P2-3 (3), R3.C3 (B)
unnamed: BOARD1.P2-2 (2), R3.C2 (W)
unnamed: BOARD1.P2-1 (1), R3.C1 (A)
unnamed: BOARD1.P4-2 (2), R4.C2 (W)
unnamed: BOARD1.P4-3 (3), R4.C3 (B)
unnamed: BOARD1.P4-1 (1), R4.C1 (A)
unnamed: AV2_OUT.CONN (T), AV2_OUT.T1 (T), AV2_OUT.T2 (T), BOARD1.OUT2 (1)
unnamed: BOARD1.LEDA2 (2), LED2.A
unnamed: BOARD1.LEDK2 (1), LED2.K (C)
unnamed: BOARD1.SUMA (1), SUM_INA.CONN (T), SUM_INA.T1 (T), SUM_INA.T2 (T)
unnamed: BOARD1.SUMB (1), SUM_INB.CONN (T), SUM_INB.T1 (T), SUM_INB.T2 (T)
unnamed: BOARD1.SUMO (1), SUM_OUT.CONN (T), SUM_OUT.T1 (T), SUM_OUT.T2 (T)
unnamed: BOARD1.SPLIT (1), SPLIT_IN.CONN (T), SPLIT_IN.T1 (T), SPLIT_IN.T2 (T)
unnamed: BOARD1.SPLOA (1), SPLIT_OUTA.CONN (T), SPLIT_OUTA.T1 (T), SPLIT_OUTA.T2 (T)
unnamed: BOARD1.SPLOB (1), SPLIT_OUTB.CONN (T), SPLIT_OUTB.T1 (T), SPLIT_OUTB.T2 (T)

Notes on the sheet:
Mirrors: Control Voltage Processor Control Card Aidan Taylor 2020 ELECTRIC NOODLE BOX
